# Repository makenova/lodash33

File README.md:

# lodash33

A promicro version of the _33 keyboard.  There are produciton files in the "gerbers" directory for the pcb and a skeleton case.
Simply upload the zip files to your PCB manufacturer of choice.

You'll also need

* Diodes (1N4148W)
  * Through hole or SMD(sod-123). Either will work
* Pro Micro(PM) or compatible board
  * I prefer something with USB C
  * You can use a nice!nano if you want to make it wireless
* Hardware
  * M2 screws
  * M2 standoffs(10mm will work if solder your PM directly or socket with low profile sockets use 12mm to be safe)

There are at least two possible layouts

Starting firmware can be found on my QMK fork in the [`makenova`](https://github.com/makenova/qmk_firmware/tree/makenova/keyboards/makenova/lodash33) branch.

Here is what a built version can look like:

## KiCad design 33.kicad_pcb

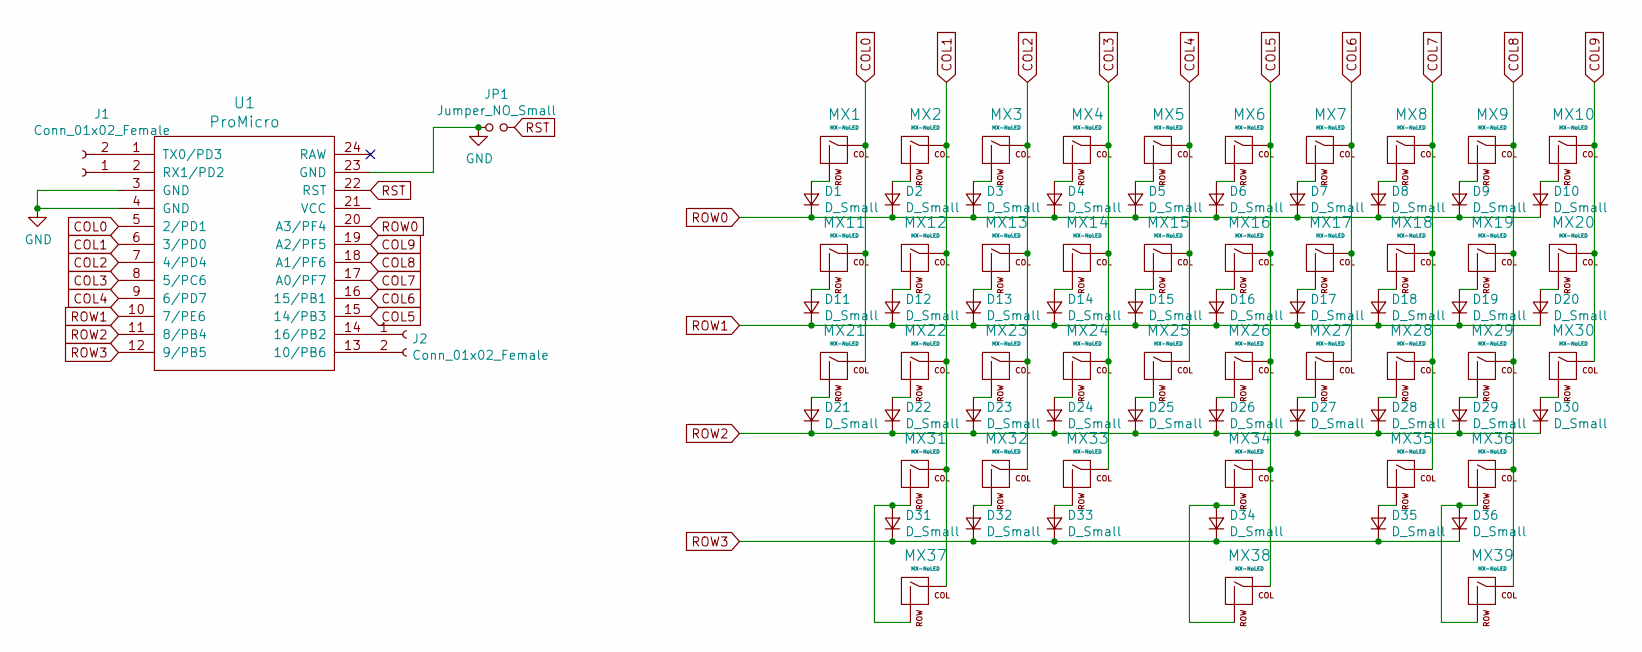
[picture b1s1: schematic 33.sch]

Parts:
D1, D2, D3, D4, D5, D6, D7, D8, D9, D10, D11, D12, D13, D14, D15, D16, D17, D18, D19, D20, D21, D22, D23, D24, D25, D26, D27, D28, D29, D30, D31, D32, D33, D34, D35, D36: D_Small; Diode-Hybrid-Back
J1, J2: Conn_01x02_Female; JST_EH_B2B-EH-A_1x02_P2.50mm_Vertical
JP1: Jumper_NO_Small; Jumper-UserFriendly-Small
MX1, MX2, MX3, MX4, MX5, MX6, MX7, MX8, MX9, MX10, MX11, MX12, MX13, MX14, MX15, MX16, MX17, MX18, MX19, MX20, MX21, MX22, MX23, MX24, MX25, MX26, MX27, MX28, MX29, MX30, MX31, MX36, MX39: MX-NoLED; MXOnly-1U-NoLED
MX32, MX35, MX37: MX-NoLED; MXOnly-1.25U-NoLED
MX33: MX-NoLED; MXOnly-2.25U-ReversedStabilizers-NoLED
MX34: MX-NoLED; MXOnly-2U-ReversedStabilizers-NoLED
MX38: MX-NoLED; MXOnly-6.25U-ReversedStabilizers-NoLED
U1: ProMicro; ArduinoProMicro-ZigZag

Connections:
COL0: MX1.1 (COL), MX11.1 (COL), MX21.1 (COL), U1.5 (2/PD1)
COL1: MX2.1 (COL), MX12.1 (COL), MX22.1 (COL), MX31.1 (COL), MX37.1 (COL), U1.6 (3/PD0)
COL2: MX3.1 (COL), MX13.1 (COL), MX23.1 (COL), MX32.1 (COL), U1.7 (4/PD4)
COL3: MX4.1 (COL), MX14.1 (COL), MX24.1 (COL), MX33.1 (COL), U1.8 (5/PC6)
COL4: MX5.1 (COL), MX15.1 (COL), MX25.1 (COL), U1.9 (6/PD7)
COL5: MX6.1 (COL), MX16.1 (COL), MX26.1 (COL), MX34.1 (COL), MX38.1 (COL), U1.15 (14/PB3)
COL6: MX7.1 (COL), MX17.1 (COL), MX27.1 (COL), U1.16 (15/PB1)
COL7: MX8.1 (COL), MX18.1 (COL), MX28.1 (COL), MX35.1 (COL), U1.17 (A0/PF7)
COL8: MX9.1 (COL), MX19.1 (COL), MX29.1 (COL), MX36.1 (COL), MX39.1 (COL), U1.18 (A1/PF6)
COL9: MX10.1 (COL), MX20.1 (COL), MX30.1 (COL), U1.19 (A2/PF5)
GND: JP1.1, U1.3 (GND), U1.4 (GND), U1.23 (GND)
unnamed: D1.2 (A), MX1.2 (ROW)
unnamed: D2.2 (A), MX2.2 (ROW)
unnamed: D3.2 (A), MX3.2 (ROW)
unnamed: D4.2 (A), MX4.2 (ROW)
unnamed: D5.2 (A), MX5.2 (ROW)
unnamed: D6.2 (A), MX6.2 (ROW)
unnamed: D7.2 (A), MX7.2 (ROW)
unnamed: D8.2 (A), MX8.2 (ROW)
unnamed: D9.2 (A), MX9.2 (ROW)
unnamed: D10.2 (A), MX10.2 (ROW)
unnamed: D11.2 (A), MX11.2 (ROW)
unnamed: D12.2 (A), MX12.2 (ROW)
unnamed: D13.2 (A), MX13.2 (ROW)
unnamed: D14.2 (A), MX14.2 (ROW)
unnamed: D15.2 (A), MX15.2 (ROW)
unnamed: D16.2 (A), MX16.2 (ROW)
unnamed: D17.2 (A), MX17.2 (ROW)
unnamed: D18.2 (A), MX18.2 (ROW)
unnamed: D19.2 (A), MX19.2 (ROW)
unnamed: D20.2 (A), MX20.2 (ROW)
unnamed: D21.2 (A), MX21.2 (ROW)
unnamed: D22.2 (A), MX22.2 (ROW)
unnamed: D23.2 (A), MX23.2 (ROW)
unnamed: D24.2 (A), MX24.2 (ROW)
unnamed: D25.2 (A), MX25.2 (ROW)
unnamed: D26.2 (A), MX26.2 (ROW)
unnamed: D27.2 (A), MX27.2 (ROW)
unnamed: D28.2 (A), MX28.2 (ROW)
unnamed: D29.2 (A), MX29.2 (ROW)
unnamed: D30.2 (A), MX30.2 (ROW)
unnamed: D31.2 (A), MX31.2 (ROW), MX37.2 (ROW)
unnamed: D32.2 (A), MX32.2 (ROW)
unnamed: D33.2 (A), MX33.2 (ROW)
unnamed: D34.2 (A), MX34.2 (ROW), MX38.2 (ROW)
unnamed: D35.2 (A), MX35.2 (ROW)
unnamed: D36.2 (A), MX36.2 (ROW), MX39.2 (ROW)
unnamed: J1.1, U1.2 (RX1/PD2)
unnamed: J1.2, U1.1 (TX0/PD3)
unnamed: J2.1, U1.14 (16/PB2)
unnamed: J2.2, U1.13 (10/PB6)
ROW0: D1.1 (K), D2.1 (K), D3.1 (K), D4.1 (K), D5.1 (K), D6.1 (K), D7.1 (K), D8.1 (K), D9.1 (K), D10.1 (K), U1.20 (A3/PF4)
ROW1: D11.1 (K), D12.1 (K), D13.1 (K), D14.1 (K), D15.1 (K), D16.1 (K), D17.1 (K), D18.1 (K), D19.1 (K), D20.1 (K), U1.10 (7/PE6)
ROW2: D21.1 (K), D22.1 (K), D23.1 (K), D24.1 (K), D25.1 (K), D26.1 (K), D27.1 (K), D28.1 (K), D29.1 (K), D30.1 (K), U1.11 (8/PB4)
ROW3: D31.1 (K), D32.1 (K), D33.1 (K), D34.1 (K), D35.1 (K), D36.1 (K), U1.12 (9/PB5)
RST: JP1.2, U1.22 (RST)

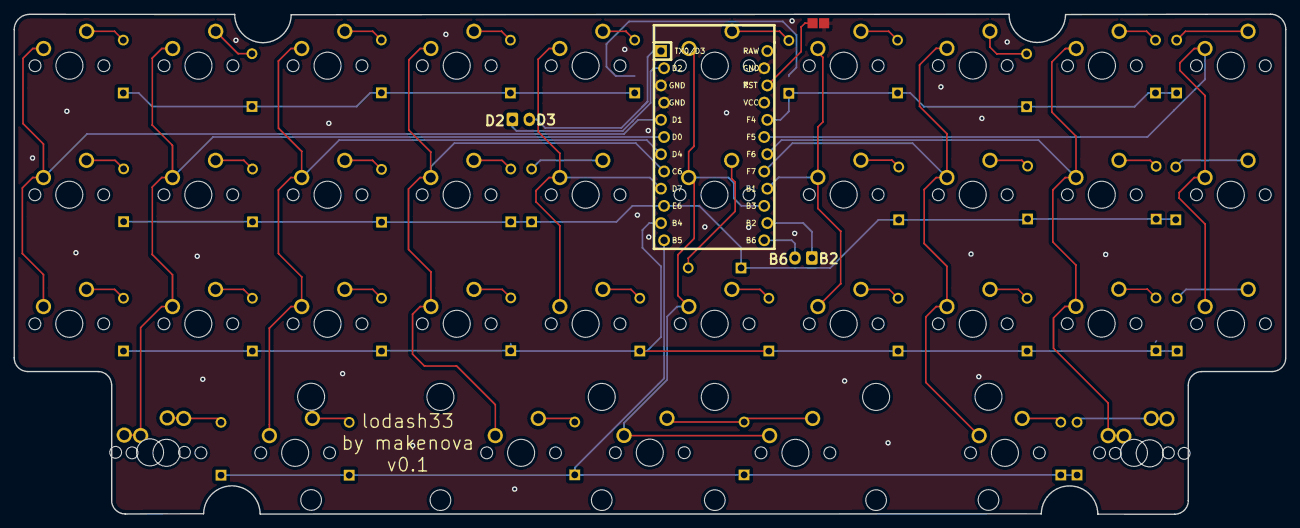
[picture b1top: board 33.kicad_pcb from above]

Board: 2 copper layers, 187.7 x 73.8 mm, 79 parts (0 on the bottom side), 56 nets.

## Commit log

2020-08-18 make it so
2020-10-15 update reset jumper position
2020-10-15 add readme
2020-10-15 add license file
2020-10-16 breakout 4 unused pins
